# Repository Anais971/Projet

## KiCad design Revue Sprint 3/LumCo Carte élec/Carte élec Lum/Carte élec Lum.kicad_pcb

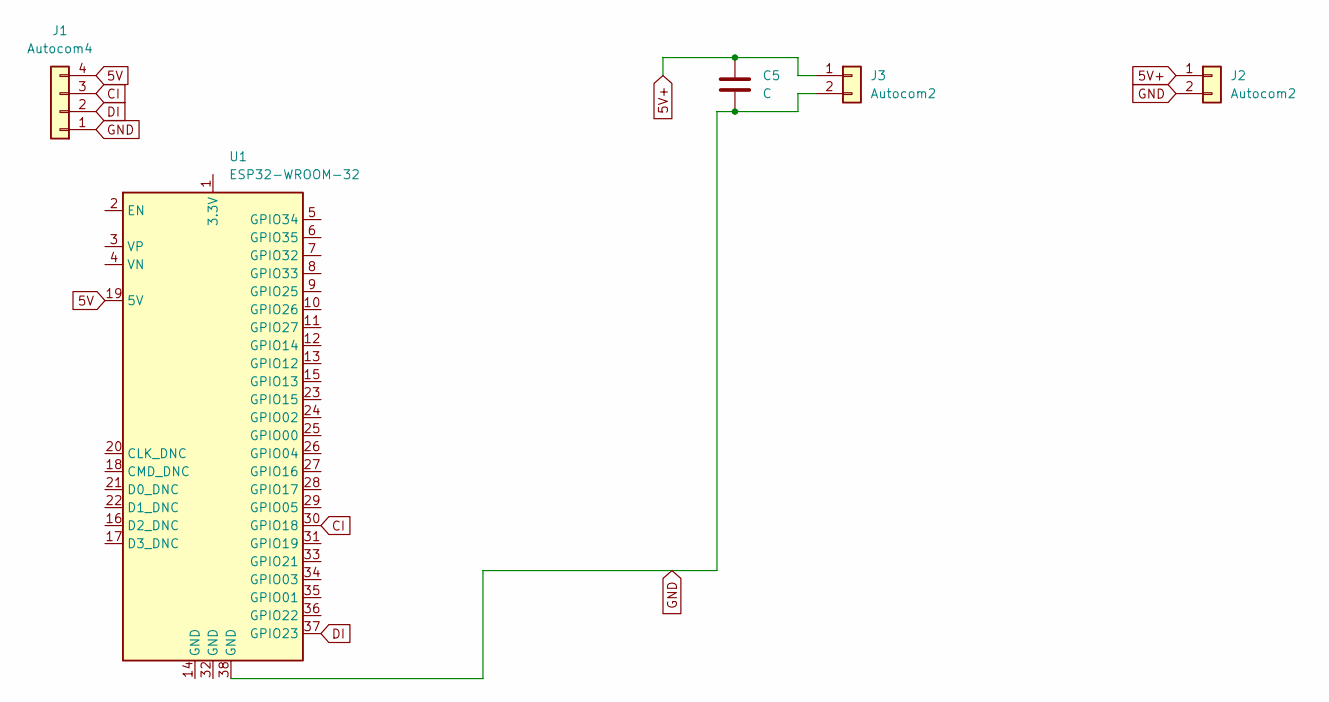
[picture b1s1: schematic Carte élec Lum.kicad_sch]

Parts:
C5: C; C_Rect_L7.0mm_W2.5mm_P5.00mm
J1: Autocom4
J2, J3: Autocom2
U1: ESP32-WROOM-32; ESP32_Module_38_pins_28mm_Wide

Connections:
5V: J1.4, U1.19 (5V)
5V+: C5.1, J2.1, J3.1
CI: J1.3, U1.30 (GPIO18)
DI: J1.2, U1.37 (GPIO23)
GND: C5.2, J1.1, J2.2, J3.2, U1.38 (GND)

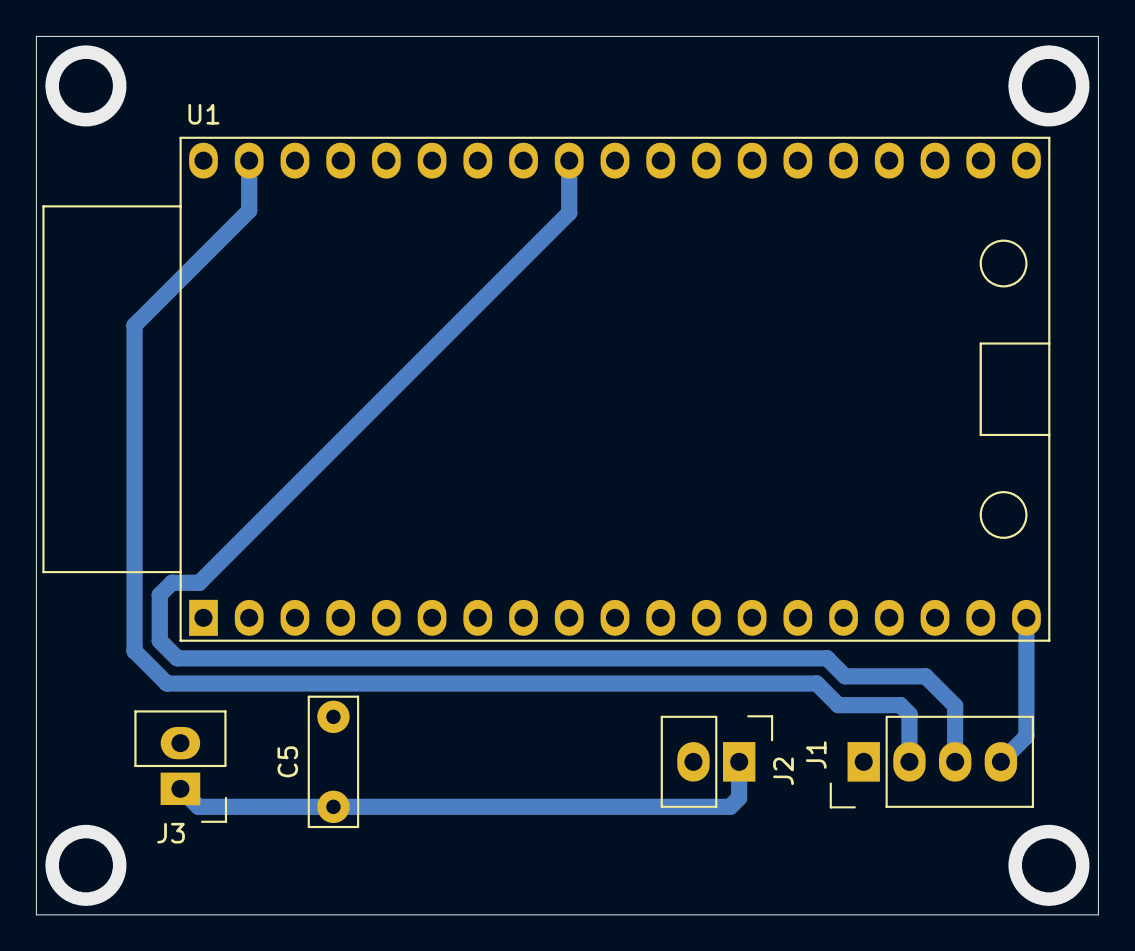
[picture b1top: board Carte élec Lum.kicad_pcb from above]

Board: 2 copper layers, 59.0 x 48.8 mm, 5 parts (0 on the bottom side), 5 nets.

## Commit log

2025-05-22 Create Prog BT android
2025-05-26 Update Prog BT android
2025-06-12 carte
2025-06-12 lampe
2025-06-18 fond
